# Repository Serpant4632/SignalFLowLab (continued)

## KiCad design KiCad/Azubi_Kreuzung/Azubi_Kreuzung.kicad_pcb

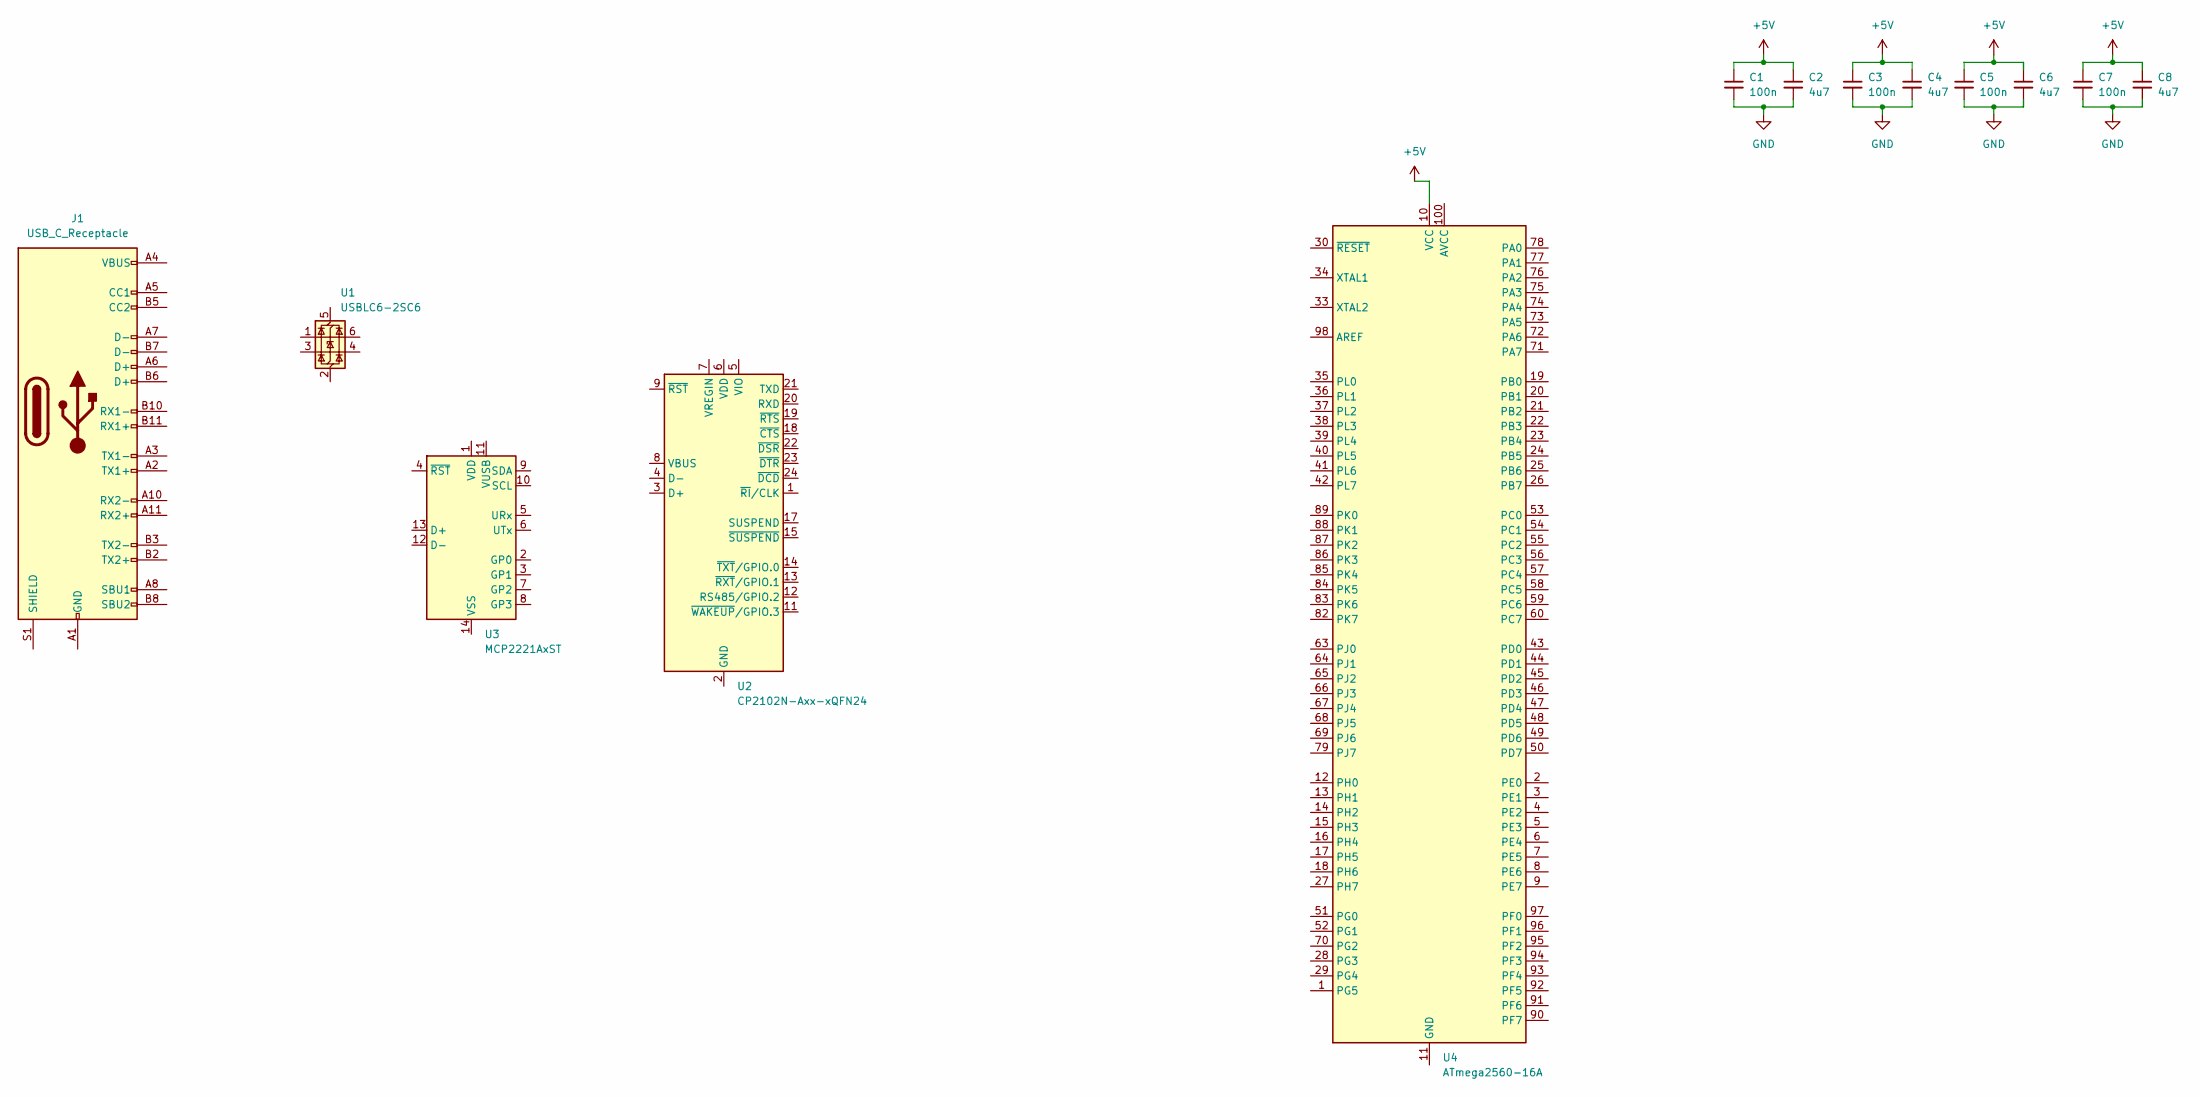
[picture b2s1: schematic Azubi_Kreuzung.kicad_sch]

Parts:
C1, C3, C5, C7: 100n; C_0402_1005Metric; LCSC C77020
C2, C4, C6, C8: 4u7; C_0603_1608Metric; LCSC C71631
J1: USB_C_Receptacle; USB_C_Receptacle_Amphenol_12401548E4-2A_CircularHoles; LCSC C3039307
U1: USBLC6-2SC6; SOT-23-6; LCSC C7519
U2: CP2102N-Axx-xQFN24; QFN-24-1EP_4x4mm_P0.5mm_EP2.6x2.6mm; LCSC C969151
U3: MCP2221AxST; TSSOP-14_4.4x5mm_P0.65mm; LCSC C130462
U4: ATmega2560-16A; TQFP-100_14x14mm_P0.5mm; LCSC C22460

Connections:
+5V: C1.1, C2.1, C3.1, C4.1, C5.1, C6.1, C7.1, C8.1, U4.10 (VCC), U4.31 (VCC), U4.61 (VCC), U4.80 (VCC)
GND: C1.2, C2.2, C3.2, C4.2, C5.2, C6.2, C7.2, C8.2
unnamed: J1.A1 (GND), J1.A12 (GND), J1.B1 (GND), J1.B12 (GND)
unnamed: J1.A4 (VBUS), J1.A9 (VBUS), J1.B4 (VBUS), J1.B9 (VBUS)
unnamed: U2.2 (GND), U2.25 (GND)
unnamed: U4.11 (GND), U4.32 (GND), U4.62 (GND), U4.81 (GND), U4.99 (GND)

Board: 2 copper layers, 13 parts (0 on the bottom side), 6 nets, no tracks yet.

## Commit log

2025-02-05 Added gitignore for KiCAD
2025-02-26 Added datasheets for used components
2025-02-26 Updatet KiCad Project files V1.1
